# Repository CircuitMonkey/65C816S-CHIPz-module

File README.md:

# 65C816S-CHIPz-module
8/16 bit 65xx CHIPz module.  Compatible with 65C02.

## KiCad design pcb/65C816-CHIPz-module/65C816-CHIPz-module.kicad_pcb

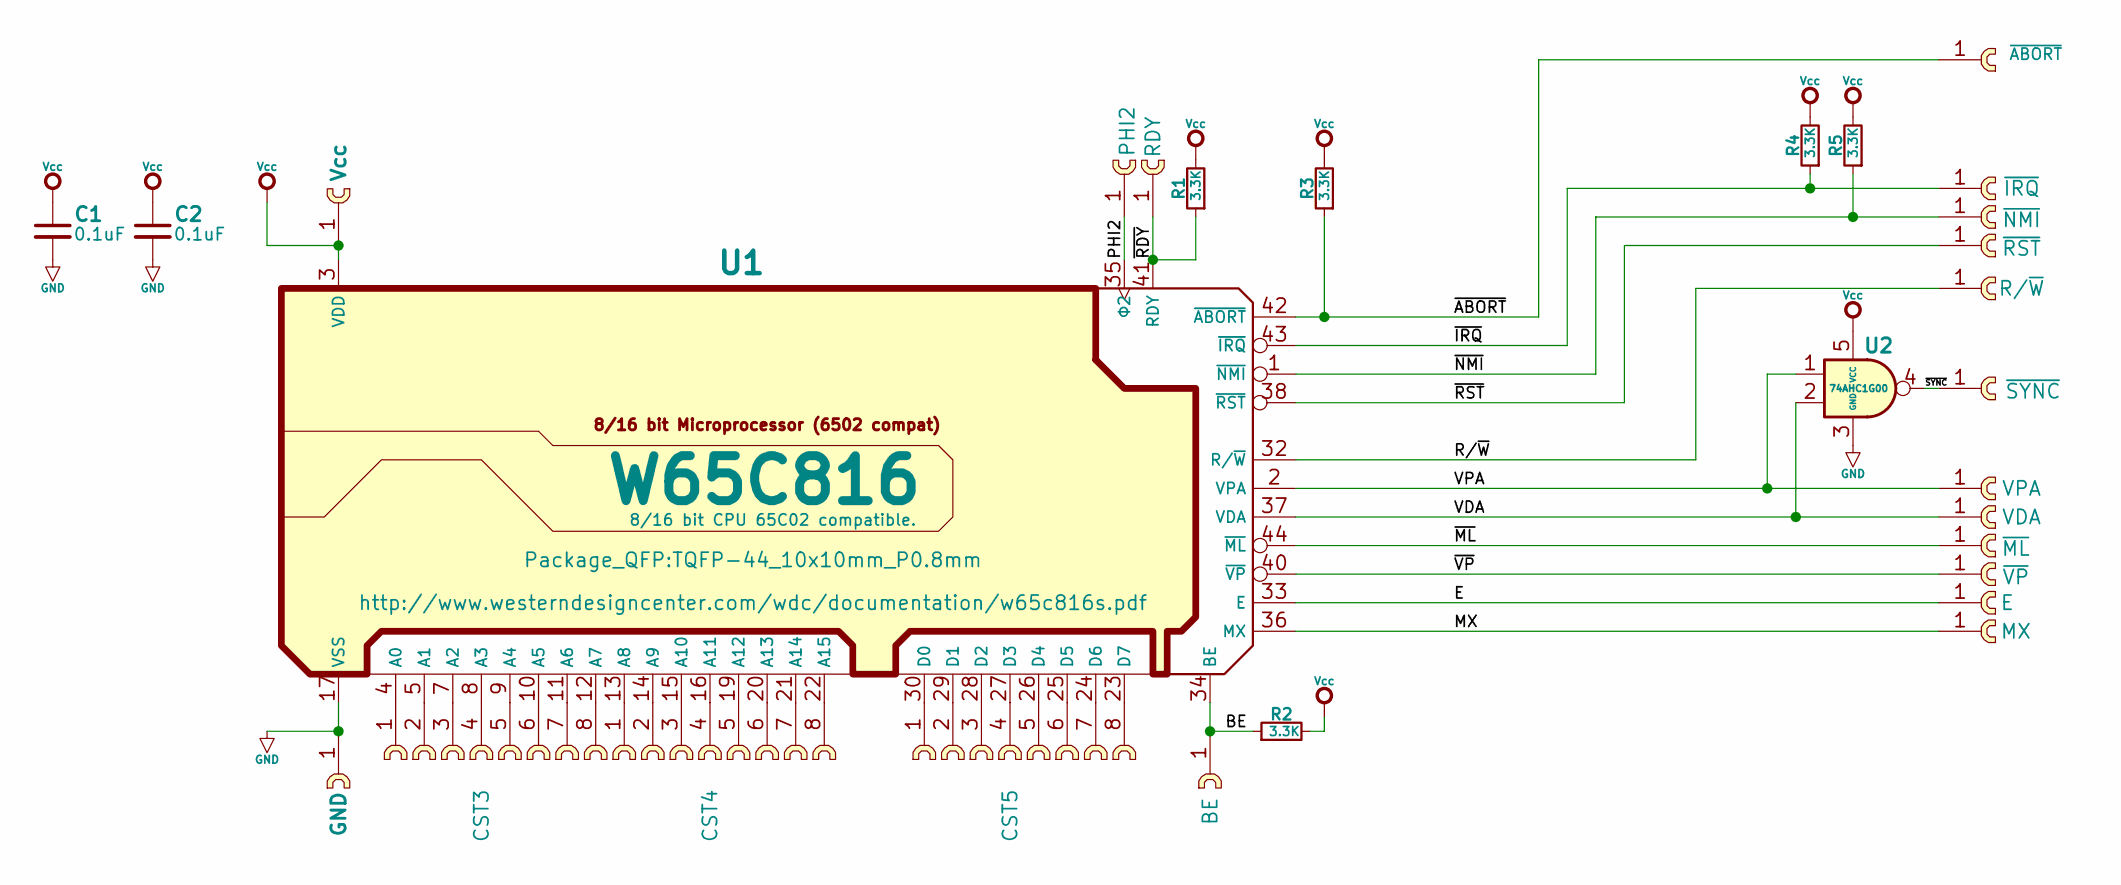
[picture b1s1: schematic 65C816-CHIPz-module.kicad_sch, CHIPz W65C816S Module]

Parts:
C1, C2: 0.1uF; C_0603_1608Metric
CST1: Vcc; cast-2.0-01P
CST2: GND; cast-2.0-01P
CST3, CST4, CST5: cast-2.0-08P
CST6: PHI2; cast-2.0-01P
CST7: RDY; cast-2.0-01P
CST8: BE; cast-2.0-01P
CST9: ~{ABORT}; cast-2.0-01P
CST10: ~{NMI}; cast-2.0-01P
CST11: ~{IRQ}; cast-2.0-01P
CST12: ~{RST}; cast-2.0-01P
CST13: R/~{W}; cast-2.0-01P
CST14: ~{SYNC}; cast-2.0-01P
CST15: VDA; cast-2.0-01P
CST16: ~{ML}; cast-2.0-01P
CST17: ~{VP}; cast-2.0-01P
CST18: E; cast-2.0-01P
CST19: MX; cast-2.0-01P
R1, R2, R3, R4, R5: 3.3K; R_0603_1608Metric
U1: W65C816; TQFP-44_10x10mm_P0.8mm
U2: 74AHC1G00; SOT-353_SC-70-5; MPN MC74HC1G00DFT1G
VPA1: VPA; cast-2.0-01P

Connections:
/BE: CST8.1, R2.1, U1.34 (BE)
/E: CST18.1, U1.33 (E)
/MX: CST19.1, U1.36 (MX)
/PHI2: CST6.1, U1.35 (Φ2)
/R/~W: CST13.1, U1.32 (R/~W)
/VDA: CST15.1, U1.37 (VDA), U2.2
/VPA: U1.2 (VPA), U2.1, VPA1.1
/~ABORT: CST9.1, R3.1, U1.42 (~ABORT)
/~IRQ: CST11.1, R4.1, U1.43 (~IRQ)
/~ML: CST16.1, U1.44 (~ML)
/~NMI: CST10.1, R5.1, U1.1 (~NMI)
/~RDY: CST7.1, R1.1, U1.41 (RDY)
/~RST: CST12.1
/~SYNC: CST14.1, U2.4
/~VP: CST17.1, U1.40 (~VP)
GND: C1.2, C2.2, CST2.1, U1.17 (VSS), U1.18 (VSS2), U1.39 (VSS3), U2.3 (GND)
unnamed: CST3.1, U1.4 (A0)
unnamed: CST3.2, U1.5 (A1)
unnamed: CST3.3, U1.7 (A2)
unnamed: CST3.4, U1.8 (A3)
unnamed: CST3.5, U1.9 (A4)
unnamed: CST3.6, U1.10 (A5)
unnamed: CST3.7, U1.11 (A6)
unnamed: CST3.8, U1.12 (A7)
unnamed: CST4.1, U1.13 (A8)
unnamed: CST4.2, U1.14 (A9)
unnamed: CST4.3, U1.15 (A10)
unnamed: CST4.4, U1.16 (A11)
unnamed: CST4.5, U1.19 (A12)
unnamed: CST4.6, U1.20 (A13)
unnamed: CST4.7, U1.21 (A14)
unnamed: CST4.8, U1.22 (A15)
unnamed: CST5.1, U1.30 (D0)
unnamed: CST5.2, U1.29 (D1)
unnamed: CST5.3, U1.28 (D2)
unnamed: CST5.4, U1.27 (D3)
unnamed: CST5.5, U1.26 (D4)
unnamed: CST5.6, U1.25 (D5)
unnamed: CST5.7, U1.24 (D6)
unnamed: CST5.8, U1.23 (D7)
Vcc: C1.1, C2.1, CST1.1, R1.2, R2.2, R3.2, R4.2, R5.2, U1.3 (VDD), U1.31 (VDD2), U2.5 (VCC)

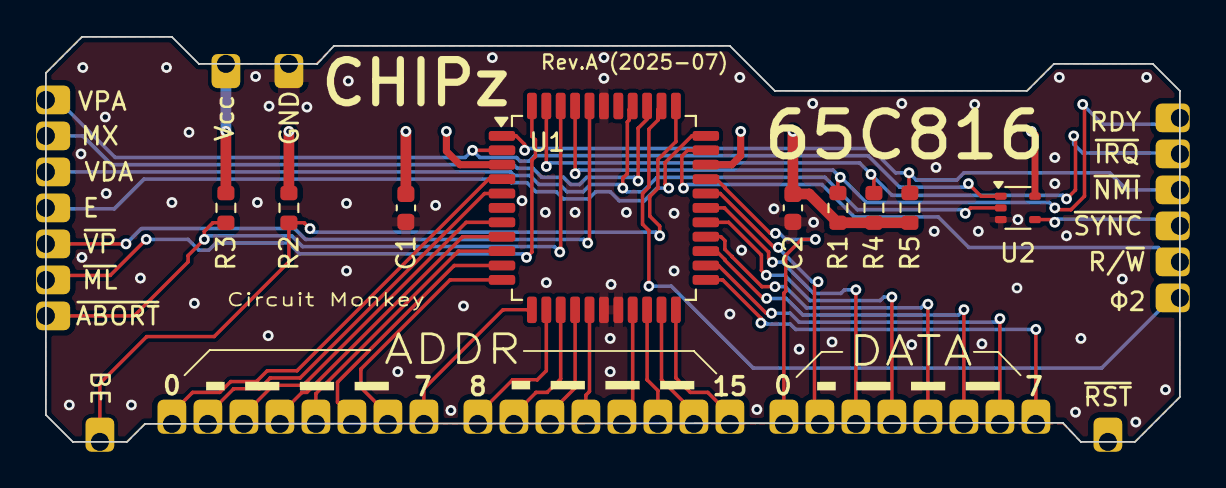
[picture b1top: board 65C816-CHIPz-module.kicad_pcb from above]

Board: 2 copper layers, 63.0 x 22.5 mm, 29 parts (0 on the bottom side), 40 nets.

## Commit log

2025-07-18 Commit Rev. A for 65C816 CHIPz module.
2025-07-18 Custom fonts not working at OSHPark, so tuned some fonts in design.
2025-07-26 Add STP file for 3D model.
2025-08-30 Add note to board.

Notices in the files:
pcb/65C816-CHIPz-module/65C816-CHIPz-module.kicad_sch:
©2025 Circuit Monkey
MIT License
